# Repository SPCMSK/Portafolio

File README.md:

# Portfolio de Ingeniería | Matias Ignacio Izaurieta Fernandez

Ingeniero Civil Electrónico (PUCV) | Embedded Systems & Prototipado IoT

## Perfil y Enfoque

Soy un estudiante de 6to año de Ingeniería Civil Electrónica de la Pontificia Universidad Católica de Valparaíso (PUCV). Mi enfoque principal se centra en el **diseño de hardware, los sistemas embebidos y la implementación de soluciones IoT**.

Me considero un profesional en formación con un marcado espíritu **autodidacta** y **"Maker"**. Este repositorio busca demostrar mi habilidad para llevar proyectos desde el concepto hasta el prototipo funcional, combinando programación de firmware (C++/ESP32) con diseño de circuitos y desarrollo de interfaces web.

## Stack Tecnológico Principal

| Categoría | Tecnologías Clave |
| :--- | :--- |
| **Firmware/Hardware** | ESP32, Arduino, C++, KiCad (Diseño PCB & 3D), Eagle, Soldadura. |
| **Programación/Software**| Next.js, TypeScript, JavaScript, Python, TailwindCSS, MATLAB. |
| **Comunicaciones/IoT** | ArtNet, MIDI, Protocolos de Red (WiFi), Impresión 3D. |

## Proyectos Destacados

### 🌐 Desarrollo Web (Fullstack & UI)

#### 1. [SSTransportes.cl](https://sstransportes.cl)
* **Descripción:** Plataforma corporativa para servicios logísticos y transporte. Implementada con un enfoque en rendimiento y escalabilidad, utilizando un stack moderno para una gestión de datos eficiente.
* **Stack:** Next.js, TypeScript, TailwindCSS.
* **Skills Clave:** Optimización de UI/UX, Despliegue (Vercel/Cloud), Tipado estricto para robustez del sitio.

#### 2. [Impcore.cl](https://www.impcore.cl/)
* **Descripción:** Creación y despliegue de una plataforma web completa de difusión musical. Muestra experiencia en el desarrollo Front-End con tecnología moderna, esencial para la visualización de datos en proyectos IoT.
* **Skills Clave:** Next.js, TypeScript, TailwindCSS.

---

### 🎹 Electrónica y Hardware (Eurorack / Audio Analógico)

He desarrollado módulos de síntesis analógica enfocados en la precisión y la integración de componentes de grado de audio, utilizando **KiCad** para el diseño de PCBs, incluyendo modelado 3D de los componentes para asegurar la integridad mecánica del hardware.

#### 3. VCO Austral (Basado en AS3340)
* **Descripción:** Oscilador controlado por voltaje de alta fidelidad. Utiliza el chip **AS3340** para garantizar un seguimiento de octava (V/Oct) extremadamente estable y formas de onda puras (Seno, Triángulo, Sierra, Pulso).
* **Capacidades:** Implementación de compensación térmica y diseño de rutas de señal de bajo ruido.

#### 4. Narcotic VCO (Basado en SSI2130)
* **Descripción:** Diseño avanzado de oscilador utilizando el chip de última generación **SSI2130**. Este proyecto demuestra mi capacidad para trabajar con circuitos integrados complejos de montaje superficial (SMD) que requieren una gestión de señales analógicas y digitales integrada.
* **Capacidades:** Diseño de PCB multi-capa en KiCad, integración de modelos 3D para fabricación y optimización de espacio.

---

### 5. SPC-8SEQ: Secuenciador MIDI de Hardware
* **Descripción:** Prototipado integral de un controlador/secuenciador MIDI de 8 pasos. Ciclo completo de desarrollo: desde la ideación y el diseño de la PCB hasta la programación de firmware en C++ para comunicación USB-MIDI de baja latencia con un ESP32.
* **Skills Clave:** C++, ESP32, Diseño PCB, MIDI, Integración de UI (OLED, Encoders).

### 6. Sistema IoT de Iluminación ArtNet
* **Descripción:** Implementación de un sistema inalámbrico de control lumínico. Configuración de nodos basados en ESP32 como receptores del protocolo ArtNet (DMX sobre IP) para la sincronización en tiempo real con software de visuales (Resolume Arena).
* **Skills Clave:** IoT, Protocolos de Red, ArtNet, ESP32, Automatización.

---

## Contacto

Si deseas revisar el CV completo o discutir oportunidades de práctica, no dudes en contactarme:

* **LinkedIn:** [https://de.linkedin.com/](https://de.linkedin.com/) (Actualiza con tu link directo)
* **Correo Electrónico:** Izaurietamatiasignacio@gmail.com

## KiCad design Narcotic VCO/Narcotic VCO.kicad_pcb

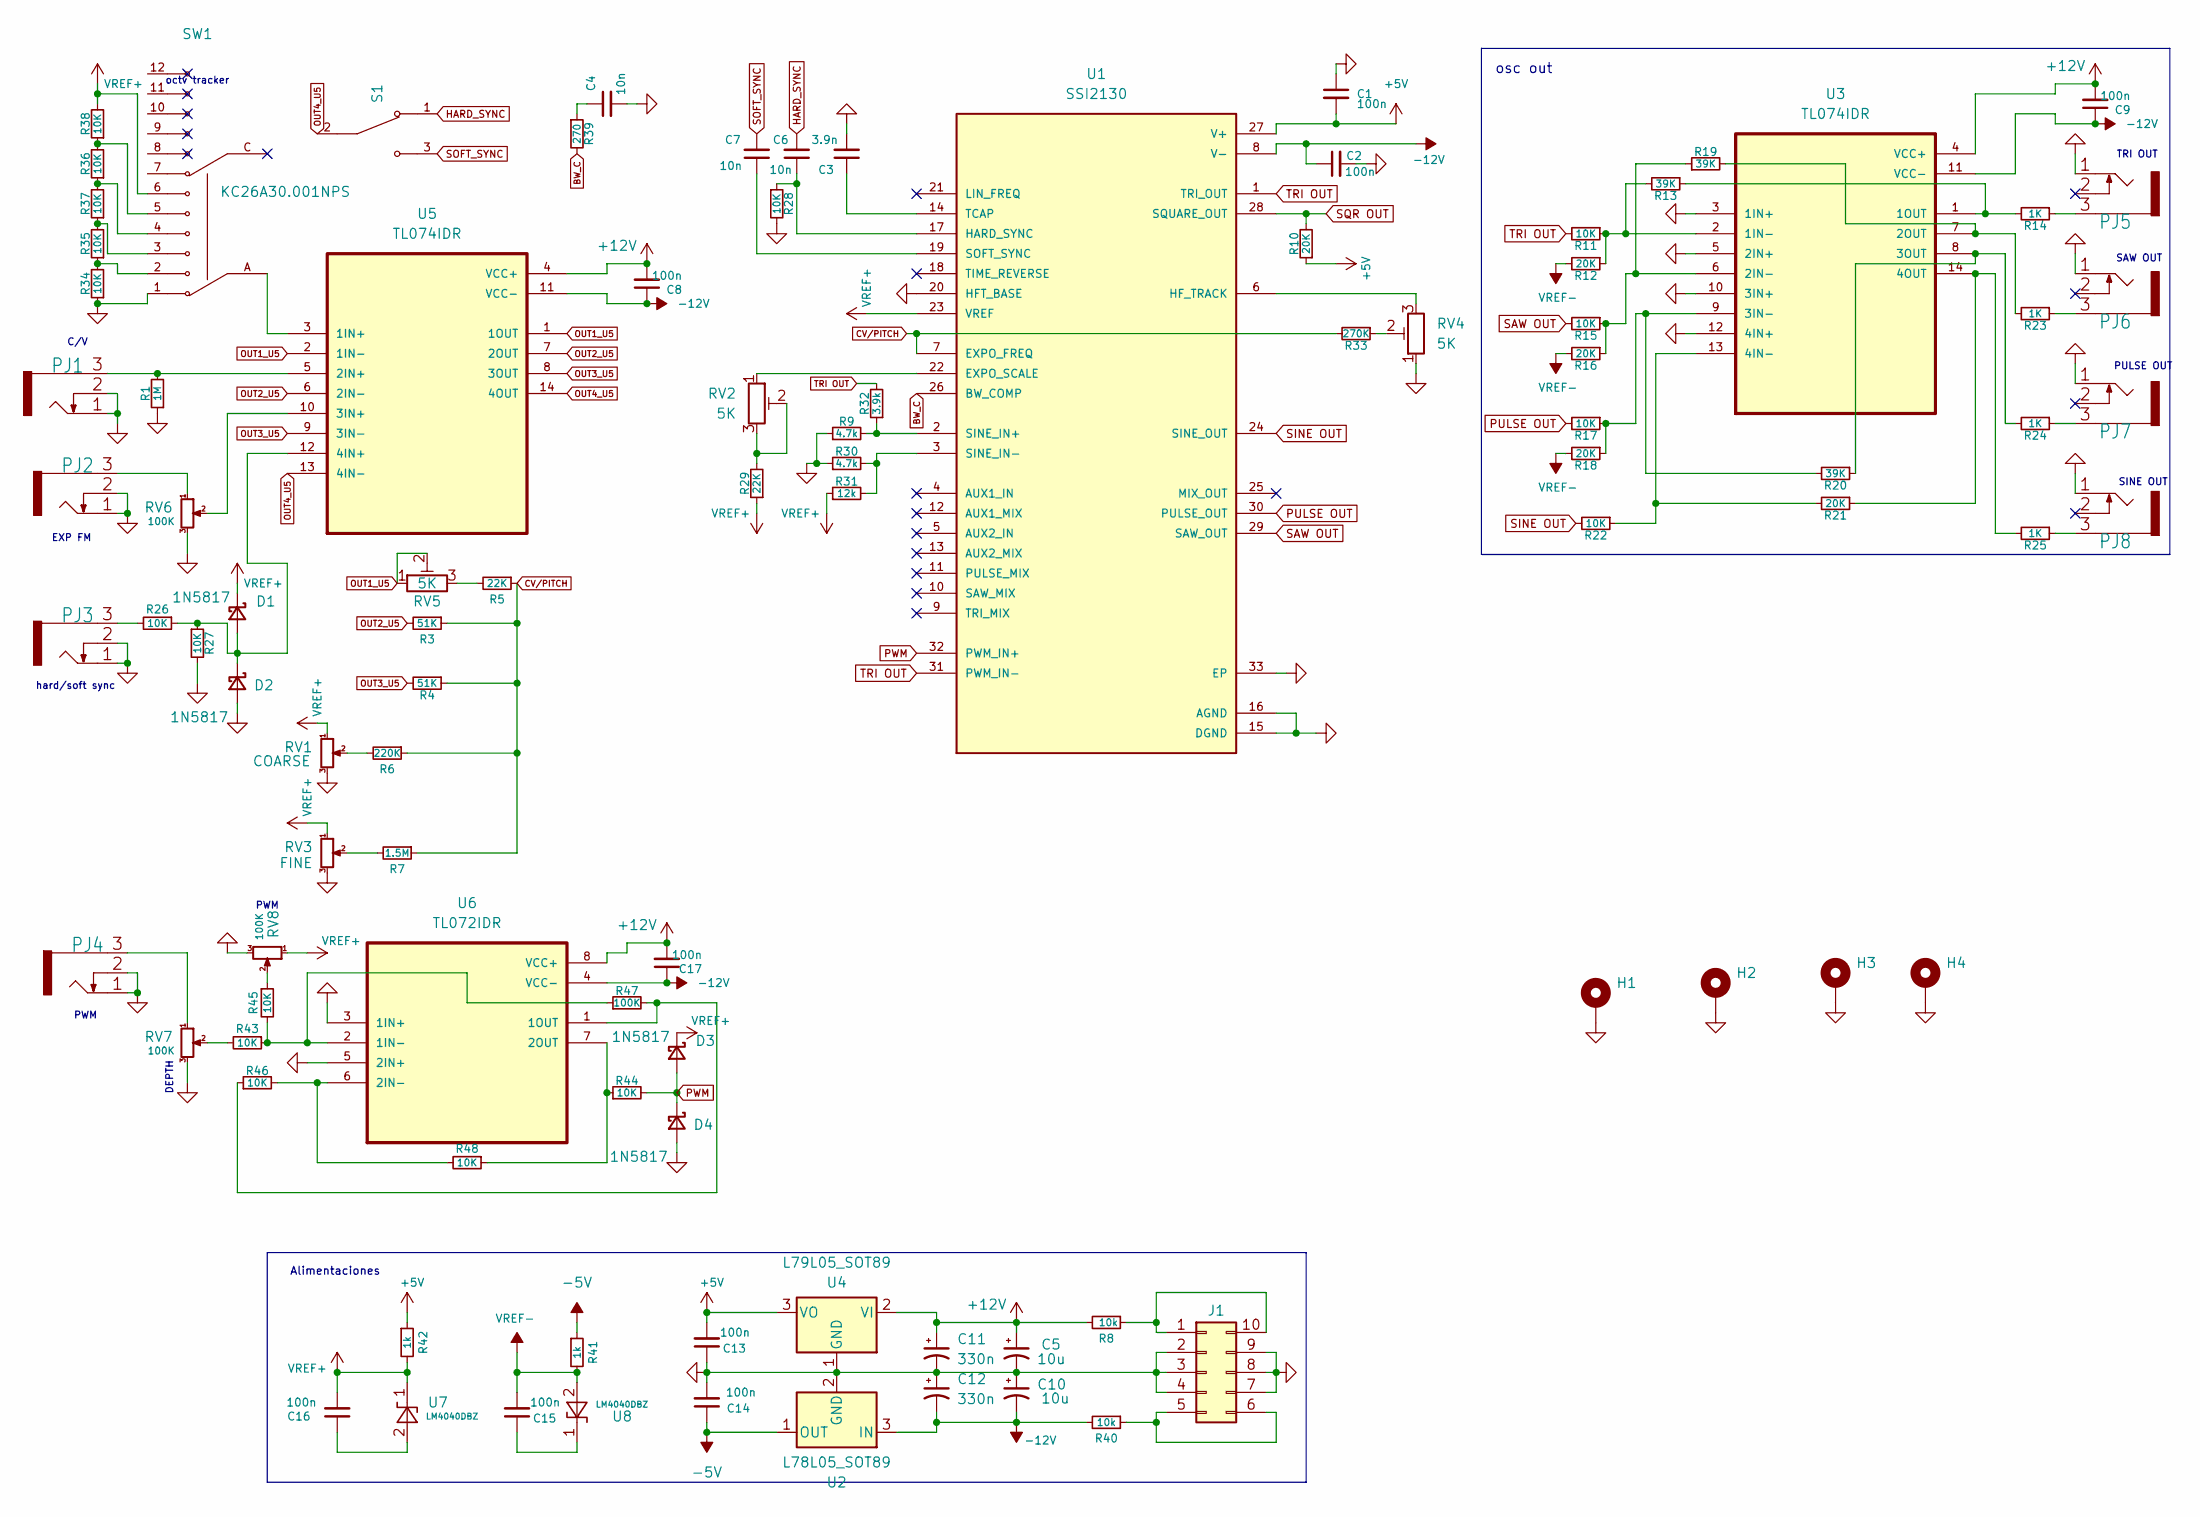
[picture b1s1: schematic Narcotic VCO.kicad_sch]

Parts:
C1, C2, C8, C9, C13, C14, C15, C16, C17: 100n; C_0805_2012Metric
C3: 3.9n; C_Rect_L7.2mm_W2.5mm_P5.00mm_FKS2_FKP2_MKS2_MKP2
C4, C6, C7: 10n; C_Rect_L7.2mm_W2.5mm_P5.00mm_FKS2_FKP2_MKS2_MKP2
C5, C10: 10u; CP_Radial_D5.0mm_P2.00mm
C11, C12: 330n; CP_Radial_D5.0mm_P2.00mm
D1, D2, D3, D4: 1N5817; D_SOD-123
H1, H2, H3, H4: MountingHole_Pad; MountingHole_3.2mm_M3_DIN965_Pad
J1: Conn_02x05_Counter_Clockwise; PinHeader_2x05_P2.54mm_Vertical
PJ1, PJ2, PJ3, PJ4, PJ5, PJ6, PJ7, PJ8: SWITCHCRAFT_MDPC2A
R1: 1M; R_Axial_DIN0207_L6.3mm_D2.5mm_P10.16mm_Horizontal
R3, R4: 51K; R_0805_2012Metric
R5, R29: 22K; R_0805_2012Metric
R6: 220K; R_0805_2012Metric
R7: 1.5M; R_Axial_DIN0207_L6.3mm_D2.5mm_P10.16mm_Horizontal
R8, R40: 10k; R_0805_2012Metric
R9, R30: 4.7k; R_0805_2012Metric
R10, R12, R16, R18, R21: 20K; R_0805_2012Metric
R11, R15, R17, R22, R26, R27, R28, R43, R44, R45, R46, R48: 10K; R_0805_2012Metric
R13, R19, R20: 39K; R_0805_2012Metric
R14, R23, R24, R25: 1K; R_0805_2012Metric
R31: 12k; R_0805_2012Metric
R32: 3.9k; R_0805_2012Metric
R33: 270K; R_0805_2012Metric
R34, R35, R36, R37, R38: 10K; R_Axial_DIN0207_L6.3mm_D2.5mm_P10.16mm_Horizontal
R39: 270; R_0805_2012Metric
R41, R42: 1k; R_0805_2012Metric
R47: 100K; R_0805_2012Metric
RV1: COARSE; POT_RD901F-40-15R1-B100K-00DL1
RV2, RV4, RV5: 5K; TRIM_3296W-1-103LF
RV3: FINE; POT_RD901F-40-15R1-B100K-00DL1
RV6, RV7, RV8: 100K; POT_RD901F-40-15R1-B100K-00DL1
S1: 100SP1T1B4M2QE; SW_100SP1T1B4M2QE; PARTREV E
SW1: KC26A30.001NPS; SW_KC26A30.001NPS; PARTREV B
U1: SSI2130; QFN40P400X400X90-33N; PARTREV Rev. 2.4
U2: L78L05_SOT89; SOT-89-3
U3, U5: TL074IDR; SOIC127P600X175-14N
U4: L79L05_SOT89; SOT-89-3
U6: TL072IDR; SOIC127P599X175-8N
U7, U8: LM4040DBZ; SOT-23

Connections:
+5V: C1.2, C13.2, R10.1, R42.1, U1.27 (V+), U4.3 (VO)
-5V: C14.1, R41.1, U2.1 (OUT)
BW_C: R39.2, U1.26 (BW_COMP)
CV/PITCH: R3.1, R4.1, R5.1, R6.1, R7.1, R33.2, U1.7 (EXPO_FREQ)
GND: C1.1, C2.2, C3.2, C4.2, C5.2, C10.1, C11.2, C12.1, C13.1, C14.2, D2.2 (A), D4.2 (A), H1.1, H2.1, H3.1, H4.1, J1.2, J1.3, J1.4, J1.7, J1.8, J1.9, PJ1.1 (2), PJ1.2 (3), PJ2.1 (2), PJ2.2 (3), PJ3.1 (2), PJ3.2 (3), PJ4.1 (2), PJ4.2 (3), PJ5.1 (2), PJ6.1 (2), PJ7.1 (2), PJ8.1 (2), R1.1, R9.1, R27.2, R28.2, R30.1, R34.1, RV1.3, RV3.3, RV4.1, RV6.3, RV7.3, RV8.3, SW1.1, U1.15 (DGND), U1.16 (AGND), U1.20 (HFT_BASE), U1.33 (EP), U2.2 (GND), U3.3 (1IN+), U3.5 (2IN+), U3.10 (3IN+), U3.12 (4IN+), U4.1 (GND), U6.3 (1IN+), U6.5 (2IN+)
HARD_SYNC: C6.2, S1.1
unnamed: C4.1, R39.1
unnamed: D1.2 (A), D2.1 (K), R26.1, R27.1, U5.12 (4IN+)
unnamed: PJ1.3 (1), R1.2, U5.5 (2IN+)
unnamed: PJ2.3 (1), RV6.1
unnamed: PJ3.3 (1), R26.2
unnamed: PJ4.3 (1), RV7.1
unnamed: PJ5.3 (1), R14.1
unnamed: PJ6.3 (1), R23.1
unnamed: PJ7.3 (1), R24.1
unnamed: PJ8.3 (1), R25.1
unnamed: R5.2, RV5.3
unnamed: R6.2, RV1.2
unnamed: R7.2, RV3.2
unnamed: R29.2, RV2.2, RV2.3
unnamed: R33.1, RV4.2
unnamed: R34.2, R35.1, SW1.2
unnamed: R35.2, R37.1, SW1.3
unnamed: R36.1, R37.2, SW1.4
unnamed: R36.2, R38.1, SW1.5
unnamed: R43.2, RV7.2
unnamed: R45.1, RV8.2
unnamed: RV2.1, U1.22 (EXPO_SCALE)
unnamed: C6.1, R28.1, U1.17 (HARD_SYNC)
unnamed: RV4.3, U1.6 (HF_TRACK)
unnamed: R9.2, R32.1, U1.2 (SINE_IN+)
unnamed: R30.2, R31.2, U1.3 (SINE_IN-)
unnamed: C7.1, U1.19 (SOFT_SYNC)
unnamed: C3.1, U1.14 (TCAP)
unnamed: R11.1, R12.1, R13.2, U3.2 (1IN-)
unnamed: R13.1, R14.2, U3.1 (1OUT)
unnamed: R15.1, R16.1, R19.1, U3.6 (2IN-)
unnamed: R19.2, R23.2, U3.7 (2OUT)
unnamed: R17.1, R18.1, R20.2, U3.9 (3IN-)
unnamed: R20.1, R24.2, U3.8 (3OUT)
unnamed: R21.2, R22.1, U3.13 (4IN-)
unnamed: R21.1, R25.2, U3.14 (4OUT)
unnamed: SW1.A, U5.3 (1IN+)
unnamed: RV6.2, U5.10 (3IN+)
unnamed: R43.1, R45.2, R47.1, U6.2 (1IN-)
unnamed: R46.1, R47.2, U6.1 (1OUT)
unnamed: R46.2, R48.2, U6.6 (2IN-)
unnamed: R44.1, R48.1, U6.7 (2OUT)
unnamed: C16.1, U7.2 (A)
unnamed: C15.1, U8.1 (K)
OUT1_U5: RV5.1, RV5.2, U5.1 (1OUT), U5.2 (1IN-)
OUT2_U5: R3.2, U5.6 (2IN-), U5.7 (2OUT)
OUT3_U5: R4.2, U5.8 (3OUT), U5.9 (3IN-)
OUT4_U5: S1.2, U5.13 (4IN-), U5.14 (4OUT)
PULSE OUT: R17.2, U1.30 (PULSE_OUT)
PWM: D3.2 (A), D4.1 (K), R44.2, U1.32 (PWM_IN+)
SAW OUT: R15.2, U1.29 (SAW_OUT)
SINE OUT: R22.2, U1.24 (SINE_OUT)
SOFT_SYNC: C7.2, S1.3
SQR OUT: R10.2, U1.28 (SQUARE_OUT)
TRI OUT: R11.2, R32.2, U1.1 (TRI_OUT), U1.31 (PWM_IN-)
VREF+: C16.2, D1.1 (K), D3.1 (K), R29.1, R31.1, R38.2, R42.2, RV1.1, RV3.1, RV8.1, SW1.6, U1.23 (VREF), U7.1 (K)
VREF-: C15.2, R12.2, R16.2, R18.2, R41.2, U8.2 (A)

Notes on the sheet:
PWM
DEPTH
PULSE OUT
osc out
SAW OUT
TRI OUT
octv tracker
SINE OUT
hard/soft sync
C/V
EXP FM
Alimentaciones

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
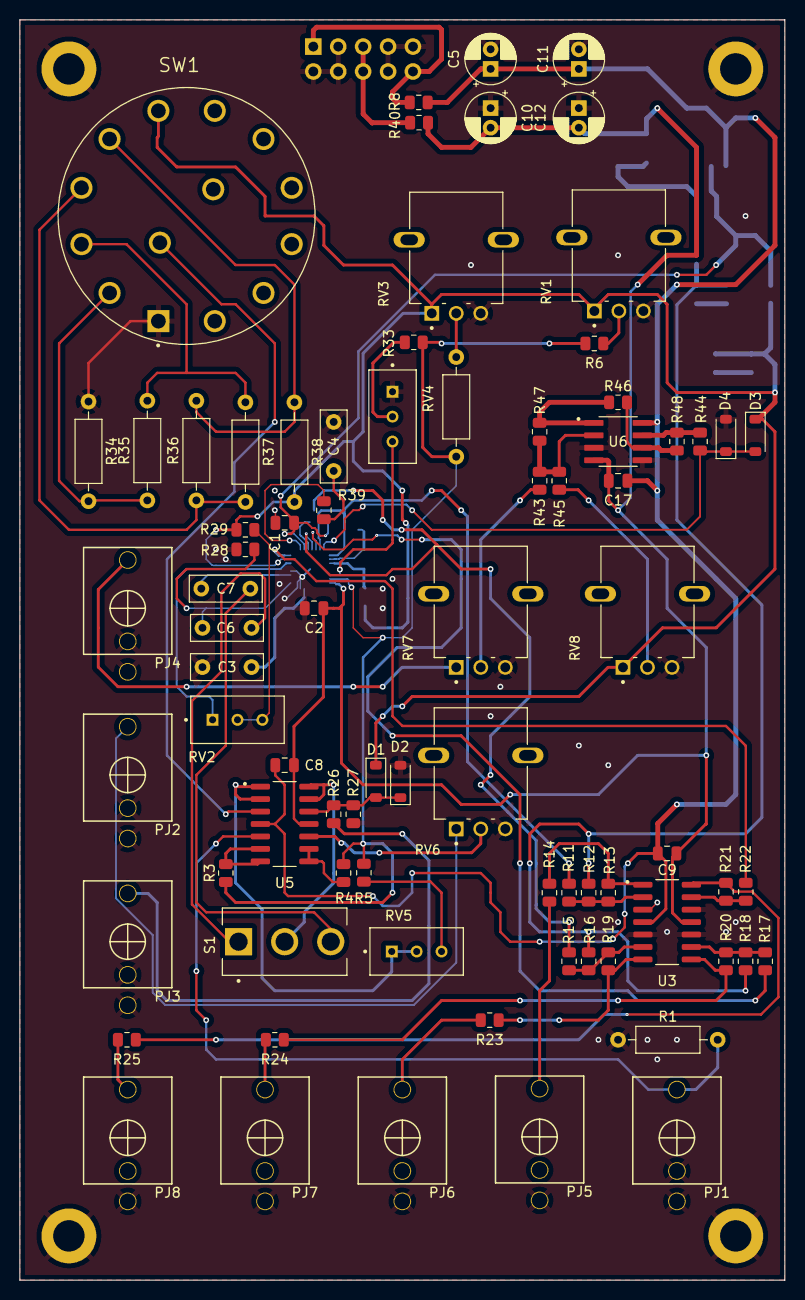
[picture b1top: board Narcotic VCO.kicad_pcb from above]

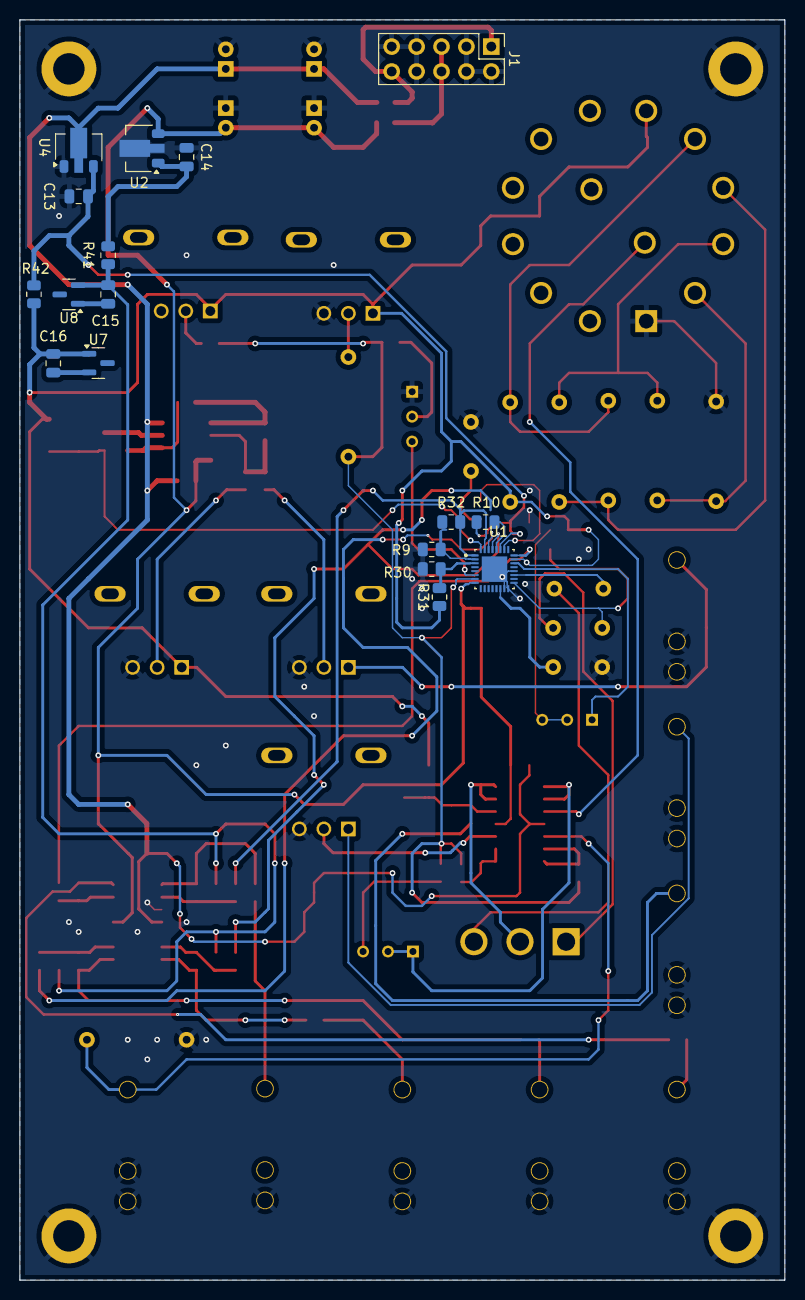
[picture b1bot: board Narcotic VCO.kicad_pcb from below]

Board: 2 copper layers, 78.0 x 128.5 mm, 99 parts (17 on the bottom side), 65 nets.

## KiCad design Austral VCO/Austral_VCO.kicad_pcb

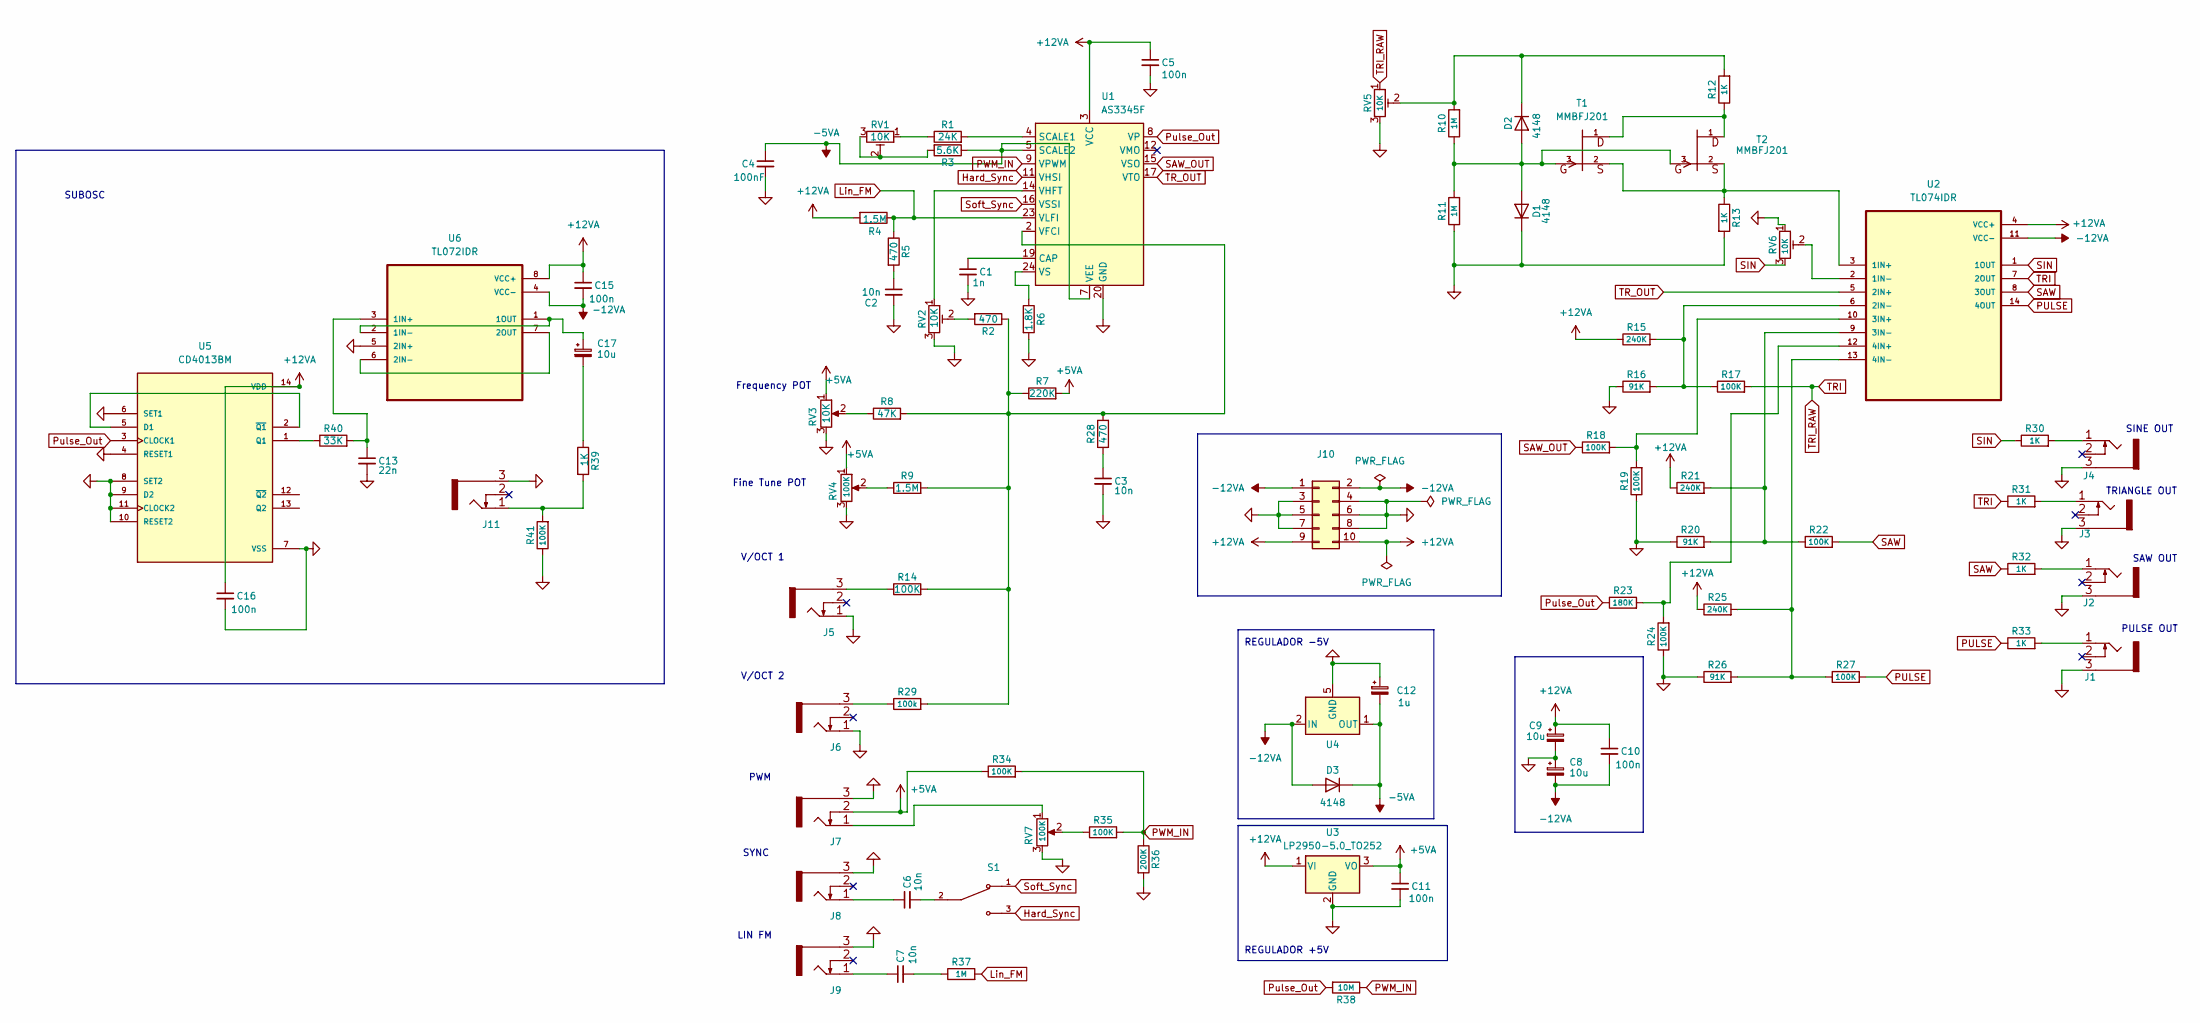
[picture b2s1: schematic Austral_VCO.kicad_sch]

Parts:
C1: 1n; C_Rect_L7.2mm_W2.5mm_P5.00mm_FKS2_FKP2_MKS2_MKP2
C2, C3, C6, C7: 10n; C_0805_2012Metric
C4: 100nF; C_0805_2012Metric
C5, C10, C11, C15, C16: 100n; C_0805_2012Metric
C8, C9, C17: 10u; CP_Radial_D5.0mm_P2.50mm
C12: 1u; CP_Radial_D5.0mm_P2.50mm
C13: 22n; C_0805_2012Metric
D1, D2, D3: 4148; D_SOD-123
J1, J2, J3, J4, J5, J6, J7, J8, J9, J11: MDPC2A; SWITCHCRAFT_MDPC2A; PARTREV F
J10: Conn_02x05_Odd_Even; PinHeader_2x08_P2.54mm_Vertical
R1: 24K; R_Axial_DIN0207_L6.3mm_D2.5mm_P7.62mm_Horizontal
R2: 470; R_Axial_DIN0207_L6.3mm_D2.5mm_P7.62mm_Horizontal
R3: 5.6K; R_Axial_DIN0207_L6.3mm_D2.5mm_P7.62mm_Horizontal
R4, R9: 1.5M; R_0805_2012Metric
R5, R28: 470; R_0805_2012Metric
R6: 1.8K; R_Axial_DIN0207_L6.3mm_D2.5mm_P7.62mm_Horizontal
R7: 220K; R_0805_2012Metric
R8: 47K; R_0805_2012Metric
R10, R11, R37: 1M; R_0805_2012Metric
R12, R13, R30, R31, R32, R33, R39: 1K; R_0805_2012Metric
R14: 100K; R_Axial_DIN0207_L6.3mm_D2.5mm_P7.62mm_Horizontal
R15, R21, R25: 240K; R_0805_2012Metric
R16, R20, R26: 91K; R_0805_2012Metric
R17, R18, R19, R22, R24, R27, R34, R35, R41: 100K; R_0805_2012Metric
R23: 180K; R_0805_2012Metric
R29: 100k; R_Axial_DIN0207_L6.3mm_D2.5mm_P7.62mm_Horizontal
R36: 200K; R_0805_2012Metric
R38: 10M; R_Axial_DIN0207_L6.3mm_D2.5mm_P7.62mm_Horizontal
R40: 33K; R_0805_2012Metric
RV1, RV2, RV5, RV6: 10K; Potentiometer_Bourns_3296W_Vertical
RV3: 10K; Potentiometer_Alpha_RD901F-40-00D_Single_Vertical
RV4, RV7: 100K; Potentiometer_Alpha_RD901F-40-00D_Single_Vertical
S1: 100SP1T1B4M2QE; SW_100SP1T1B4M2QE; PARTREV E
T1, T2: MMBFJ201; SOT-23-3
U1: AS3345F; QFN-24-1EP_4x4mm_P0.5mm_EP2.7x2.7mm
U2: TL074IDR; SOIC127P600X175-14N
U3: LP2950-5.0_TO252; TO-252-2
U4: L79L05_SO8; SOIC-8_3.9x4.9mm_P1.27mm
U5: CD4013BM; SOIC127P600X175-14N; PARTREV E
U6: TL072IDR; SOIC127P599X175-8N

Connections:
+5VA: C11.1, J7.2 (3), R7.2, R34.1, RV3.1, RV4.1, U3.3 (VO)
+12VA: C5.1, C9.1, C10.1, C15.1, C16.1, J10.9, J10.10, R4.2, R15.1, R21.1, R25.1, U1.3 (VCC), U2.4 (VCC+), U3.1 (VI), U5.14 (VDD), U6.8 (VCC+)
-5VA: C4.1, C12.2, D3.1 (K), R3.1, U1.5 (SCALE2), U1.7 (VEE), U4.1 (OUT)
-12VA: C8.2, C10.2, C15.2, D3.2 (A), J10.1, J10.2, U2.11 (VCC-), U4.2 (IN), U4.3 (IN), U4.6 (IN), U4.7 (IN), U6.4 (VCC-)
GND: C1.2, C2.2, C3.2, C4.2, C5.2, C8.1, C9.2, C11.2, C12.1, C13.2, C16.2, D1.1 (K), J1.3 (1), J2.3 (1), J3.3 (1), J4.3 (1), J5.1 (2), J6.1 (2), J7.3 (1), J8.3 (1), J9.3 (1), J10.3, J10.4, J10.5, J10.6, J10.7, J10.8, J11.3 (1), R6.2, R11.1, R13.2, R16.1, R19.1, R20.1, R24.1, R26.1, R36.2, R41.1, RV2.3, RV3.3, RV4.3, RV5.3, RV6.1, RV7.3, U1.20 (GND), U1.22 (GND), U3.2 (GND), U4.5 (GND), U5.4 (RESET1), U5.6 (SET1), U5.7 (VSS), U5.8 (SET2), U5.9 (D2), U5.10 (RESET2), U5.11 (CLOCK2), U6.5 (2IN+)
Hard_Sync: S1.3, U1.11 (VHSI)
Lin_FM: R4.1, R5.1, R37.2, U1.23 (VLFI)
unnamed: C2.1, R5.2
unnamed: C3.1, R28.1
unnamed: C6.2, S1.2
unnamed: C7.2, R37.1
unnamed: C17.2, R39.1
unnamed: D1.2 (A), D2.2 (A), R10.1, R11.2, T1.3, T2.3
unnamed: D2.1 (K), R10.2, R12.2, RV5.2
unnamed: J1.1 (2), R33.2
unnamed: J2.1 (2), R32.2
unnamed: J3.1 (2), R31.2
unnamed: J4.1 (2), R30.2
unnamed: J5.3 (1), R14.1
unnamed: J6.3 (1), R29.1
unnamed: J7.1 (2), RV7.1
unnamed: C6.1, J8.1 (2)
unnamed: C7.1, J9.1 (2)
unnamed: J11.1 (2), R39.2, R41.2
unnamed: R1.1, RV1.1
unnamed: R2.2, RV2.2
unnamed: R3.2, RV1.2, RV1.3
unnamed: R8.1, RV3.2
unnamed: R9.1, RV4.2
unnamed: R12.1, T1.1, T2.1
unnamed: R35.1, RV7.2
unnamed: C1.1, U1.19 (CAP)
unnamed: R1.2, U1.4 (SCALE1)
unnamed: R2.1, R7.1, R8.2, R9.2, R14.2, R28.2, R29.2, U1.2 (VFCI)
unnamed: RV2.1, U1.14 (VHFT)
unnamed: R6.1, U1.24 (VS)
unnamed: R13.1, T1.2, T2.2, U2.3 (1IN+)
unnamed: RV6.2, U2.2 (1IN-)
unnamed: R15.2, R16.2, R17.1, U2.6 (2IN-)
unnamed: R18.2, R19.2, U2.10 (3IN+)
unnamed: R20.2, R21.2, R22.1, U2.9 (3IN-)
unnamed: R23.2, R24.2, U2.12 (4IN+)
unnamed: R25.2, R26.2, R27.1, U2.13 (4IN-)
unnamed: U5.2 (~Q1), U5.5 (D1)
unnamed: R40.1, U5.1 (Q1)
unnamed: C13.1, R40.2, U6.3 (1IN+)
unnamed: C17.1, U6.1 (1OUT), U6.2 (1IN-)
unnamed: U6.6 (2IN-), U6.7 (2OUT)
PULSE: R27.2, R33.1, U2.14 (4OUT)
PWM_IN: R34.2, R35.2, R36.1, R38.1, U1.9 (VPWM)
Pulse_Out: R23.1, R38.2, U1.8 (VP), U5.3 (CLOCK1)
SAW: R22.2, R32.1, U2.8 (3OUT)
SAW_OUT: R18.1, U1.15 (VSO)
SIN: R30.1, RV6.3, U2.1 (1OUT)
Soft_Sync: S1.1, U1.16 (VSSI)
TRI: R17.2, R31.1, RV5.1, U2.7 (2OUT)
TR_OUT: U1.17 (VTO), U2.5 (2IN+)

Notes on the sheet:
REGULADOR -5V
SINE OUT
Fine Tune POT
PULSE OUT
LIN FM
TRIANGLE OUT
SAW OUT
SYNC
Frequency POT
V/OCT 1
PWM
V/OCT 2
SUBOSC
REGULADOR +5V

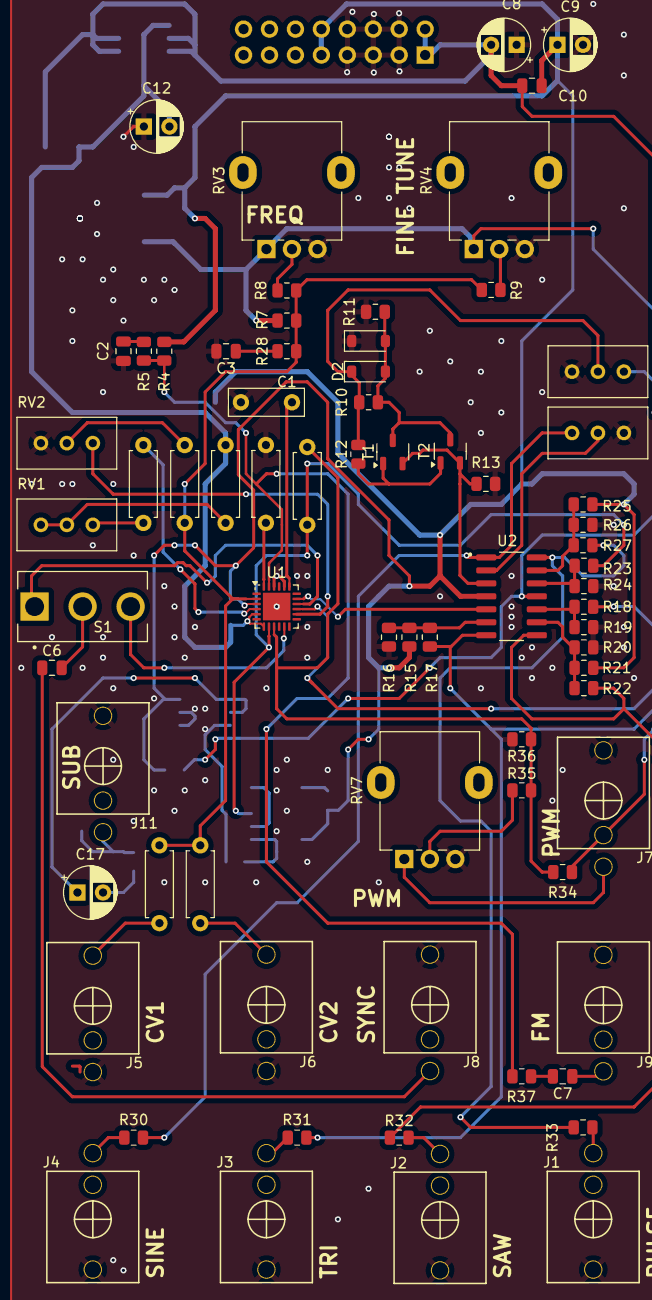
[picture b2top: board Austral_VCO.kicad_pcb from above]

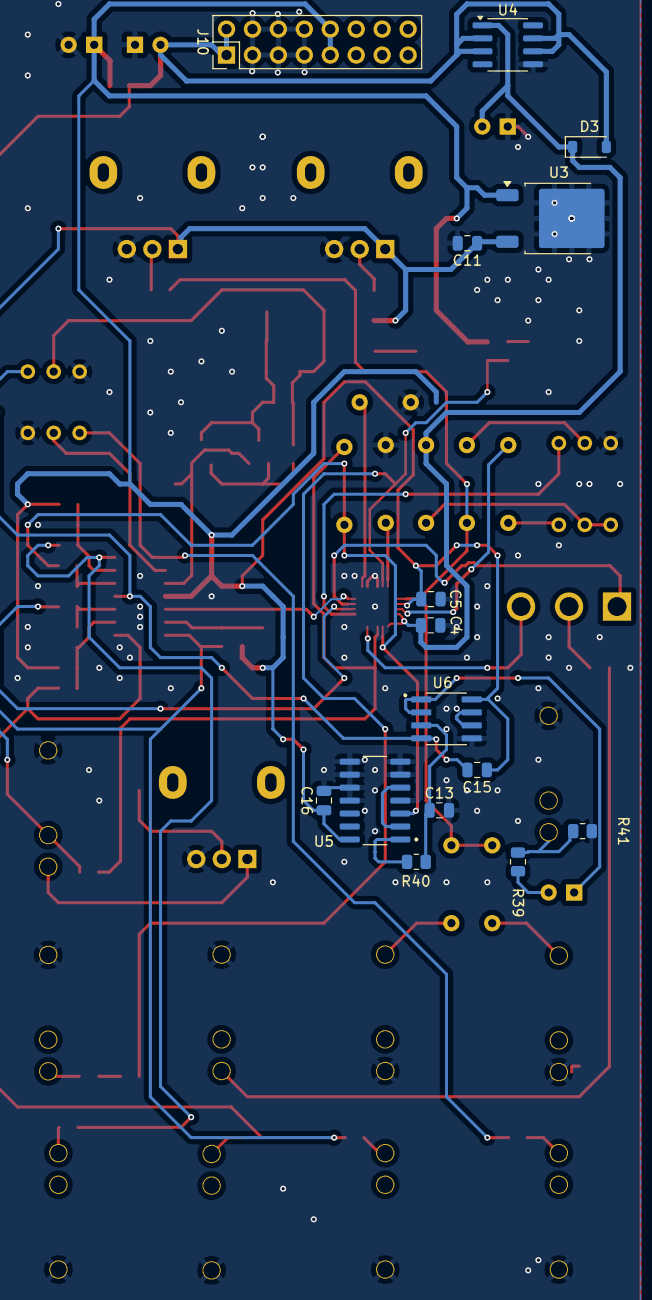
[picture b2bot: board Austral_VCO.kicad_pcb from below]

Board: 2 copper layers, 87 parts (15 on the bottom side), 57 nets.

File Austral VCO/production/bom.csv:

Designator,Footprint,Quantity,Value,LCSC Part #
C1,C_Rect_L7.2mm_W2.5mm_P5.00mm_FKS2_FKP2_MKS2_MKP2,1,1n,
"C10, C11, C15, C16, C5",0805,5,100n,
C12,CP_Radial_D5.0mm_P2.50mm,1,1u,
C13,0805,1,22n,
"C17, C8, C9",CP_Radial_D5.0mm_P2.50mm,3,10u,
"C2, C3, C6, C7",0805,4,10n,
C4,0805,1,100nF,
"D1, D2, D3",D_SOD-123,3,4148,
"J1, J11, J2, J3, J4, J5, J6, J7, J8, J9",SWITCHCRAFT_MDPC2A,10,MDPC2A,
J10,PinHeader_2x08_P2.54mm_Vertical,1,Conn_02x05_Odd_Even,
R1,R_Axial_DIN0207_L6.3mm_D2.5mm_P7.62mm_Horizontal,1,24K,
"R10, R11, R37",0805,3,1M,
"R12, R13, R30, R31, R32, R33, R39",0805,7,1K,
"R14, R29",R_Axial_DIN0207_L6.3mm_D2.5mm_P7.62mm_Horizontal,2,100K,
"R15, R21, R25",0805,3,240K,
"R16, R20, R26",0805,3,91K,
"R17, R18, R19, R22, R24, R27, R34, R35, R41",0805,9,100K,
R2,R_Axial_DIN0207_L6.3mm_D2.5mm_P7.62mm_Horizontal,1,470,
R23,0805,1,180K,
"R28, R5",0805,2,470,
R3,R_Axial_DIN0207_L6.3mm_D2.5mm_P7.62mm_Horizontal,1,5.6K,
R36,0805,1,200K,
R38,R_Axial_DIN0207_L6.3mm_D2.5mm_P7.62mm_Horizontal,1,10M,
"R4, R9",0805,2,1.5M,
R40,0805,1,33K,
R6,R_Axial_DIN0207_L6.3mm_D2.5mm_P7.62mm_Horizontal,1,1.8K,
R7,0805,1,220K,
R8,0805,1,47K,
"RV1, RV2, RV5, RV6",Potentiometer_Bourns_3296W_Vertical,4,10K,
RV3,Potentiometer_Alpha_RD901F-40-00D_Single_Vertical,1,10K,
"RV4, RV7",Potentiometer_Alpha_RD901F-40-00D_Single_Vertical,2,100K,
S1,SW_100SP1T1B4M2QE,1,100SP1T1B4M2QE,
"T1, T2",SOT-23-3,2,MMBFJ201,
U1,QFN-24-1EP_4x4mm_P0.5mm_EP2.7x2.7mm,1,AS3345F,
U2,SOIC127P600X175-14N,1,TL074IDR,
U3,TO-252-2,1,LP2950-5.0_TO252,
U4,SOIC-8_3.9x4.9mm_P1.27mm,1,L79L05_SO8,
U5,SOIC127P600X175-14N,1,CD4013BM,
U6,SOIC127P599X175-8N,1,TL072IDR,
